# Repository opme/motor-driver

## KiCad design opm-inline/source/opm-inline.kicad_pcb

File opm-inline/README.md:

# motor-driver

This motor driver uses inline current sensing.  The driver chip TMC6200 has built in current sensing.

# Diagram

# TMC6200 Gate Driver

Design uses TMC6200 gate driver.  The datasheet is located at .  Below are some high level details about the gate driver.

Universal high voltage BLDC/PMSM/Servo MOSFET 3-halfbridge gate-driver with in line motor current sensing. External MOSFETs for up to 100A motor current. 3 Floating Sense Amplifiers with programmable gain (5, 10, 20)

Integrated current sense amplifiers eliminate costly sense amplifiers required for FOC controllers (recommended use for applications up to 10A, use external precision amplifiers for higher current with low sense resistor values)

THE TMC6200 OFFERS TWO BASIC MODES OF OPERATION: 

MODE 1: Stand-alone driver with pin configuration 
Enable this mode by tying low pin SPE. The interface pins allow a number of different settings for
BBM generation and sense amplifier amplification control. 

MODE 2: SPI controlled 
This mode allows detailed control over the protection, diagnostic and control features, e.g. for tuning
overcurrent detection. Enable this mode by tying high pin SPE.

The driver integrates a four-level temperature sensor (120°C pre-warning and selectable 136°C / 143°C / 150°C thermal shutdown)

The TMC6200 protects the MOSFET power stages against a short circuit or overload condition by monitoring the voltage drop in the high-side MOSFETs, as well as the voltage drop in the low-side mosfets

# Design Discussion

Choice is to run in Mode 1 - Stand-alone driver with pin configuration.  See datasheet Figure 1.1 Standalone application using differential sensing.  Existing FOC algorithms should run without relying on the SPI interface.  Future versions could change if the controller firmware has a driver added for TMC6200. 

In this mode the SPI pins are used for configuration and not settings/diagnostics.  Setting SDO/Single to +VCC_IO allow signals to be set to DRV_EN.  This is also the case for the Drive Strength and the sense amplication.  In a 10A implementation we set sense amplification to 10 and 00 driver strength since we are using simialr mosfets that were tested in the datasheet.

Drive Strength:
CSN / IDRV0 and SCK / IDRV1 - 00: 0.5A 01: 0.5/1A, 10: 1A, 11: 1.5A, currently set to 00 for .5A

Sense Amplification:
SDI / AMPLx10 - Sense Amplification 0: 5, 1: 10, currently set to 10.

The TMC6200 IC current sensing is recommended to have a limit of 10A when using the internal sensing.  

The thermal design of the PCB is also designed for 10A max current.  The 10A limit is chosen to allow full SMT and single side hole through components with 1oz copper.

Heatsink over the gate driver and mosfets is required over a certain current.  28x28x20 is a standard heat sink size and is added to the pcb using silicon thermal glue.

Initial parts were selected based on the Trinamic reference designs that I have copied into this git repo.

Footprint for capacitors and resistors chosen as 0603 to make it easier to manufacture with low end SMD machines.

Parts are selected that are available in quantity from various resellers due to current chip shortage.  Avoided any parts that were only available in small quantities or not in stock.

Sense resistor selection. TMC6200 datasheet specifies different sense resistor selection.  Sense resistor of 005R0 with 10x amplification was selected for 15A max current 10A continuous.

In addition to the TMC6200 internal temperature sensor, there is a temperature sensor on the board.  The analog temperature signal is sent out the controller.

Mosfet selection.  Reference design has via for +VM connection through SMT pad.  This limits the vendor ability to manufacture the board and increases cost due to those needed to be capped in the manufacturing process.  Alternative is to put the via next to the SMT pad.

# Resistor for LED

Blue LED to show VCC power is on:
  VCC power has a range of 12V to 48V
  LED voltage is 3.1V and typical current is 5mA with absolute maximum of 25mA
  (48v - 3.1v)/ .005A = 8980 Ohm 
  (48v - 3.1v)/ .025A = 1788 Ohm
  2k resistor

RED LED for fault:  
  +VCC_IO can have a voltage between 3.3 and 5V
  (3.3v - 2.2v) / .005A = 220 Ohm
  (5v - 2.2v) / .005A = 560 Ohm
  200 Ohm resistor

# Design Discussion for TMC6200 Pins 

See TMC6200 datasheet for full documentation of pins.  Below is specific decisions taken when choice was given.

CLK 24 pin on the TMC6200 is tied to GND using short wire for internal clock.  This clock has accuracy of +-4%

Exposed die pad: Connect the exposed die pad to a GND plane. Provide as many as possible vias for heat transfer to GND plane.  Reference design has via for GND connection through SMT pad.  Since TMC chip will be manually added for first batch, these through hole vias were used.  If those are done by SMT in the future then some other solution for tying the pad to GRD may be needed.

Mosfet pads go to +VM but do not use hole through vias.  This limits the vendor ability to manufacture the board and increases cost due to those needed to be capped in the manufacturing process.  Alternative is to put the via next to the SMT pad which is done in this design.

# Part selection

| Type| Designator| Footprint| Discussion | 
| :---:  | :-:       | :-:      |  :-: |
| TerminalBlock_3_P5.08mm| U3| Libraries:TerminalBlock_bornier-3_P5.08mm| Should support 18A to 20A max current though design current is 10A | 
| 1nF/100V| C14 C12 C11| Capacitor_SMD:C_0603_1608Metric|  |
| TerminalBlock_2_P5.08mm| U2| Libraries:TerminalBlock_bornier-2_P5.08mm| |
| 330uF/63V| C15 C16| Capacitor_THT:C_Radial_D10.0mm_H20.0mm_P5.00mm| TMC6200 datasheet recommends 100uF of electroltyic capacitor for each amp of current expected.  Total 660 uF for 10 Amps included. 10000 hour life, low impedance, low ESR, high ripple current rating  |
| VCC_IO| J2| Connector_JST:JST_PH_B2B-PH-K_1x02_P2.00mm_Vertical| |
| 1000R/1%| R19 R21| Resistor_SMD:R_0603_1608Metric| |
| 19-217/GHC-YR1S2/3T| D1 D2| LED_SMD:LED_0603_1608Metric| |
| 150R/1%| R20| Resistor_SMD:R_0603_1608Metric| |
| 4700R/1%| R18 R17 R24| Resistor_SMD:R_0603_1608Metric| |
| 10000R/1%| R16| Resistor_SMD:R_0603_1608Metric| |
| 100nF/50V| C17 C20 C10| Capacitor_SMD:C_0603_1608Metric| |
| Temperature| J5| Connector_JST:JST_PH_B2B-PH-K_1x02_P2.00mm_Vertical| |
| PWMx6| J3| Connector_JST:JST_PH_B6B-PH-K_1x06_P2.00mm_Vertical| |
| 0R| R22| Resistor_SMD:R_0603_1608Metric| |
| 1500R/1%| R23| Resistor_SMD:R_0603_1608Metric| |
| Current Sensing| J6| Connector_JST:JST_PH_B3B-PH-K_1x03_P2.00mm_Vertical| |
| SPI/Info| J1| Connector_JST:JST_PH_B6B-PH-K_1x06_P2.00mm_Vertical| |
| 0R| R26| Resistor_SMD:R_0603_1608Metric| |
| 0Ω| R25| Resistor_SMD:R_0603_1608Metric| |
| 2.2uF/50V| C13 C19| Capacitor_SMD:C_0805_2012Metric| |
| 100nF/100V| C18| Capacitor_SMD:C_0805_2012Metric| |
| TMC6200-TA| IC1| Libraries:TMC6200-TA| |
| 2R2/1%| R4 R6 R11 R13 R3 R1| Resistor_SMD:R_0603_1608Metric| slope control resistors.  1Ohm to 2.2Ohm recommended for larger MOSFETs. |
| 10R/1%| R5 R12 R2| Resistor_SMD:R_0603_1608Metric| |
| 0R005/1%/1W| R9 R10 R14 R15 R7 R8| Resistor_SMD:R_1206_3216Metric| Use low inductivity SMD type, e.g. 1210 or 2512 resistor for RS|
| 4.7uF/100V| C8 C9 C7| Capacitor_SMD:C_1210_3225Metric| |
| 4.7uF/16V| C5 C4 C6| Capacitor_SMD:C_0603_1608Metric| Bootstrap capacitors.  for larger QG - use minimum 4.7µF on 12VOUT pin. QG is 59.5nC at VDS=48V, VGS=10V, ID=20A |
| 22nF/100V| C1| Capacitor_SMD:C_0603_1608Metric| |
| 100nF/100V| C2 C3| Capacitor_SMD:C_0603_1608Metric| |
| Power Mosfet 60V 100A  2.5 max Rds(on)| Q2 Q6 Q4 Q3 Q1 Q5| Libraries:PDFN-8| HYG025N06LS1C2, 60V minimum, 2.5ohm max Rds(on) and fast switching for lower heat dissipation, Max current > 30A|

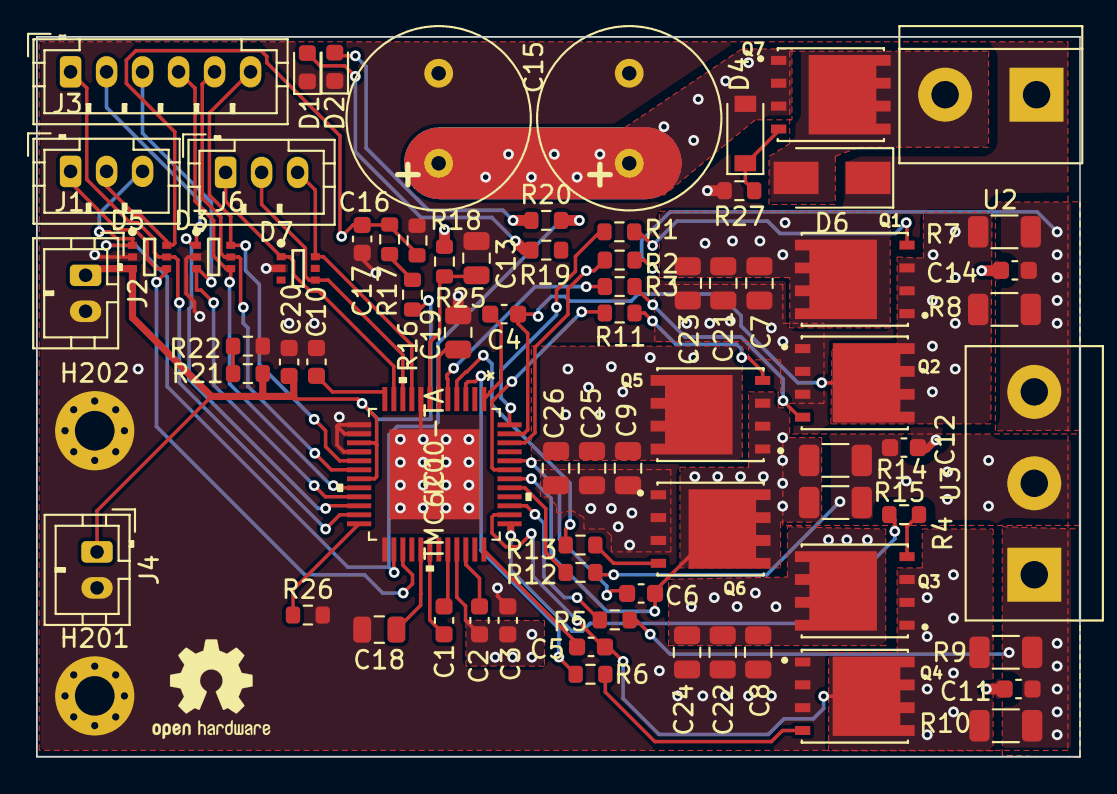
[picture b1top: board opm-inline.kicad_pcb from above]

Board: 4 copper layers, 58.0 x 40.0 mm, 76 parts (0 on the bottom side), 53 nets.

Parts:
C1: 22nF/100V; C_0603_1608Metric
C2, C3: 100nF/100V; C_0603_1608Metric
C4: 4.7uF/16V; C_0603_1608Metric
C5, C6: 4.7UF/16V; C_0603_1608Metric
C7, C8, C9, C21, C22, C23, C24, C25, C26: 1uF/100V; C_0805_2012Metric
C10, C17, C20: 100nF/50V; C_0603_1608Metric
C11, C12, C14: 1nF/100V; C_0603_1608Metric
C13, C19: 2.2uF/50V; C_0805_2012Metric
C15, C16: 330uF/63V; C_Radial_D10.0mm_H20.0mm_P5.00mm
C18: 100nF/100V; C_0805_2012Metric
D1: Blue LED; LED_0603_1608Metric
D2: Red LED; LED_0603_1608Metric
D3, D5, D7: NUP4114UCW1T2G
D4: 10V; D_SOD-123
D6: TVS DIODE; D_SMA
H201, H202: MountingHole; MountingHole_2.2mm_M2_Pad_Via
HS1: Heatsink; OSHW-Logo2_7.3x6mm_SilkScreen
IC1: TMC6200-TA
J1: Info; JST_PH_B3B-PH-K_1x03_P2.00mm_Vertical
J2: VCC_IO; JST_PH_B2B-PH-K_1x02_P2.00mm_Vertical
J3: PWMx6; JST_PH_B6B-PH-K_1x06_P2.00mm_Vertical
J4: Fan; JST_PH_B2B-PH-K_1x02_P2.00mm_Vertical
J6: Current Sensing; JST_PH_B3B-PH-K_1x03_P2.00mm_Vertical
Q1, Q2, Q3, Q4, Q5, Q6: HYG025N06LS1C2; PDFN-8
Q7: WSD90P06DN56; PDFN-8
R1, R3, R4, R6, R11, R13: 2R2/1%; R_0603_1608Metric
R2, R5, R12: 10R/1%; R_0603_1608Metric
R7, R8, R9, R10, R14, R15: 0R005/1%/1W; R_1206_3216Metric
R16: 10000R/1%; R_0603_1608Metric
R17, R18: 4700R/1%; R_0603_1608Metric
R19: 2KR/1%; R_0603_1608Metric
R20: 200R/1%; R_0603_1608Metric
R21: 1000R/1%; R_0603_1608Metric
R22, R26: 0R; R_0603_1608Metric
R25: 0Ω; R_0603_1608Metric
R27: 100KR; R_0603_1608Metric
U2: TerminalBlock_2_P5.08mm; TerminalBlock_bornier-2_P5.08mm
U3: TerminalBlock_3_P5.08mm; TerminalBlock_bornier-3_P5.08mm

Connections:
/5Vout: C13.1, IC1.7 (5VOUT), R25.1
/12Vout: C19.1, IC1.6 (12VOUT)
/+VCC_IO: C20.1, D5.3 (K), IC1.15 (SDI/AMPLx10), IC1.19 (VCC_IO), J2.1, J4.1, R16.1, R21.1
/+VM: C2.1, C3.1, C7.1, C8.1, C9.1, C15.1, C16.1, C21.1, C22.1, C23.1, C24.1, C25.1, C26.1, D4.2 (K), IC1.33 (VS), Q1.5 (D), Q1.6 (D), Q1.7 (D), Q1.8 (D), Q3.5 (D), Q3.6 (D), Q3.7 (D), Q3.8 (D), Q5.5 (D), Q5.6 (D), Q5.7 (D), Q5.8 (D), Q7.1 (S), Q7.2 (S), Q7.3 (S), R25.2
/ADC_I_u: D7.6 (K), IC1.9 (CURU), J6.3
/ADC_I_v: D7.4 (K), IC1.10 (CURV), J6.2
/ADC_I_w: D7.1 (K), IC1.11 (CURW), J6.1
/Connectors/VOFS: R21.2, R22.1
/DRV_EN: D5.4 (K), IC1.27 (DRV_EN), J1.1
/FAULT: D5.1 (K), IC1.26 (FAULT), J1.3, R20.2
/Motor Driver/VOFS: C10.1, IC1.12 (VOFS/TEST)
/TEMP_PCB: C17.1, D5.6 (K), J1.2, R17.2, R18.1
/U: C14.1, R2.1, R7.1, R8.1, U3.3
/UH: D3.6 (K), IC1.17 (UH), J3.6
/UL: D3.5 (K), IC1.18 (UL), J3.5
/V: C12.1, R12.1, R14.1, R15.1, U3.2
/VH: D3.4 (K), IC1.20 (VH), J3.4
/VL: D3.3 (K), IC1.21 (VL), J3.3
/VSA: C18.1, IC1.29 (VSA)
/W: C11.1, R5.1, R9.1, R10.1, U3.1
/WH: D3.1 (K), IC1.22 (WH), J3.2
/WL: D5.5 (K), IC1.23 (WL), J3.1
GND: C3.2, C7.2, C8.2, C9.2, C10.2, C11.2, C12.2, C13.2, C14.2, C15.2, C16.2, C17.2, C18.2, C19.2, C20.2, C21.2, C22.2, C23.2, C24.2, C25.2, C26.2, D1.1 (K), D2.1 (K), D3.2 (A), D5.2 (A), D6.1 (A), D7.2 (A), H201.1, H202.1, IC1.8 (GNDA), IC1.13 (CS/IDRV0), IC1.14 (SCK/IDRV1), IC1.16 (SDO_SINGLE), IC1.25 (SPE), IC1.EPAD, J2.2, J4.2, Q2.1 (S), Q2.2 (S), Q2.3 (S), Q4.1 (S), Q4.2 (S), Q4.3 (S), Q6.1 (S), Q6.2 (S), Q6.3 (S), R18.2, R22.2, R26.2, R27.2, U2.1
unnamed: C1.1, IC1.30 (CPO)
unnamed: C1.2, IC1.32 (CPI)
unnamed: C2.2, IC1.34 (VCP)
unnamed: C4.1, IC1.47 (U), Q1.1 (S), Q1.2 (S), Q1.3 (S), Q2.5 (D), Q2.6 (D), Q2.7 (D), Q2.8 (D), R7.2, R8.2
unnamed: C4.2, IC1.1 (CU)
unnamed: C5.1, IC1.36 (CW)
unnamed: C5.2, IC1.38 (W), Q3.1 (S), Q3.2 (S), Q3.3 (S), Q4.5 (D), Q4.6 (D), Q4.7 (D), Q4.8 (D), R9.2, R10.2
unnamed: C6.1, IC1.42 (V), Q5.1 (S), Q5.2 (S), Q5.3 (S), Q6.5 (D), Q6.6 (D), Q6.7 (D), Q6.8 (D), R14.2, R15.2
unnamed: C6.2, IC1.44 (CV)
unnamed: D1.2 (A), R19.1
unnamed: D2.2 (A), R20.1
unnamed: D4.1 (A), Q7.4 (G), R27.1
unnamed: D6.2 (K), Q7.5 (D), Q7.6 (D), Q7.7 (D), Q7.8 (D), U2.2
unnamed: IC1.3 (LSW), R6.2
unnamed: IC1.4 (LSV), R13.2
unnamed: IC1.5 (LSU), R3.2
unnamed: IC1.24 (CLK), R26.1
unnamed: IC1.37 (HSW), R4.2
unnamed: IC1.39 (WSENSE), R5.2
unnamed: IC1.41 (VSENSE), R12.2
unnamed: IC1.43 (HSV), R11.2
unnamed: IC1.46 (USENSE), R2.2
unnamed: IC1.48 (HSU), R1.2
unnamed: Q1.4 (G), R1.1
unnamed: Q2.4 (G), R3.1
unnamed: Q3.4 (G), R4.1
unnamed: Q4.4 (G), R6.1
unnamed: Q5.4 (G), R11.1
unnamed: Q6.4 (G), R13.1
unnamed: R16.2, R17.1

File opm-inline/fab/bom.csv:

Comment,Designator,Footprint,LCSC
0R,R26,Resistor_SMD:R_0603_1608Metric,C21189
100nF/50V,"C20,C10,C17",Capacitor_SMD:C_0603_1608Metric,C14663
0Ω,R25,Resistor_SMD:R_0603_1608Metric,C21189
2.2uF/50V,"C13,C19",Capacitor_SMD:C_0805_2012Metric,C49217
100nF/100V,C18,Capacitor_SMD:C_0805_2012Metric,C106243
TMC6200-TA,IC1,Libraries:TMC6200-TA,
2R2/1%,"R4,R6,R11,R13,R3,R1",Resistor_SMD:R_0603_1608Metric,C22939
10R/1%,"R5,R12,R2",Resistor_SMD:R_0603_1608Metric,C22859
0R005/1%/1W,"R9,R10,R14,R15,R7,R8",Resistor_SMD:R_1206_3216Metric,C601096
4.7UF/16V,"C5,C6",Capacitor_SMD:C_0603_1608Metric,C19666
22nF/100V,C1,Capacitor_SMD:C_0603_1608Metric,C313105
100nF/100V,"C2,C3",Capacitor_SMD:C_0603_1608Metric,C106243
4.7uF/16V,C4,Capacitor_SMD:C_0603_1608Metric,C19666
HYG025N06LS1C2,"Q2,Q6,Q4,Q3,Q1,Q5",Libraries:PDFN-8,C2827231
1uF/100V,"C9,C7,C8,C21,C23,C25,C26,C22,C24",Capacitor_SMD:C_0805_2012Metric,C697607
TerminalBlock_3_P5.08mm,U3,Libraries:TerminalBlock_bornier-3_P5.08mm,C72334
1nF/100V,"C14,C12,C11",Capacitor_SMD:C_0603_1608Metric,C342905
TerminalBlock_2_P5.08mm,U2,Libraries:TerminalBlock_bornier-2_P5.08mm,C8465
330uF/63V,"C15,C16",Capacitor_THT:C_Radial_D10.0mm_H20.0mm_P5.00mm,C338235
VCC_IO,J2,Connector_JST:JST_PH_B2B-PH-K_1x02_P2.00mm_Vertical,C131337
1000R/1%,"R19,R21",Resistor_SMD:R_0603_1608Metric,C21190
Green LED,D1,LED_SMD:LED_0603_1608Metric,C72043
150R/1%,R20,Resistor_SMD:R_0603_1608Metric,C22808
Red LED,D2,LED_SMD:LED_0603_1608Metric,C2286
4700R/1%,"R18,R17,R24",Resistor_SMD:R_0603_1608Metric,C23162
10000R/1%,R16,Resistor_SMD:R_0603_1608Metric,C13564
PWMx6,J3,Connector_JST:JST_PH_B6B-PH-K_1x06_P2.00mm_Vertical,C265365
0R,R22,Resistor_SMD:R_0603_1608Metric,
1500R/1%,R23,Resistor_SMD:R_0603_1608Metric,C22843
Current Sensing,J6,Connector_JST:JST_PH_B3B-PH-K_1x03_P2.00mm_Vertical,C131339
Fan,J4,Connector_JST:JST_PH_B2B-PH-K_1x02_P2.00mm_Vertical,C131337
Info,J1,Connector_JST:JST_PH_B3B-PH-K_1x03_P2.00mm_Vertical,C131339
100KR,R27,Resistor_SMD:R_0603_1608Metric,C25803
10V,D4,Diode_SMD:D_SOD-123,C82084
WSD90P06DN56,Q7,Libraries:PDFN-8,C719104
NUP4114UCW1T2G,"D5,D3,D7",Libraries:NUP4114UCW1T2G,C463643
TVS DIODE,D6,Diode_SMD:D_SMA,C523249

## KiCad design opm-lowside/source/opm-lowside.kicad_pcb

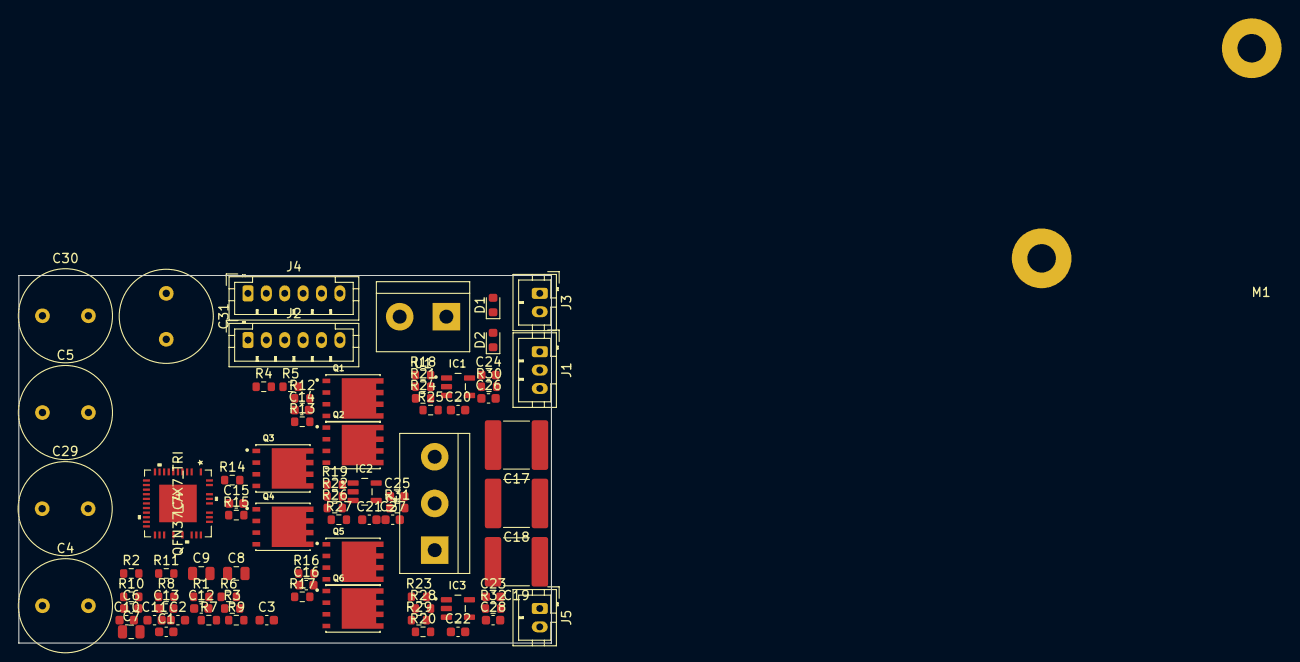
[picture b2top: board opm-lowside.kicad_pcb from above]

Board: 2 copper layers, 58.0 x 40.0 mm, 84 parts (0 on the bottom side), 65 nets, no tracks yet.

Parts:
C1, C2, C3: 1nF/100V; C_0603_1608Metric
C4, C5, C29, C30, C31: 330uF/63V; C_Radial_D10.0mm_H20.0mm_P5.00mm
C6, C10: 100nF/50V; C_0603_1608Metric
C7: 100nF/100V; C_0805_2012Metric
C8, C9: 2,2uF/50V; C_0805_2012Metric
C11: 22nF/100V; C_0603_1608Metric
C12, C13: 100nF/100V; C_0603_1608Metric
C14, C15, C16: 470nF/16V; C_0603_1608Metric
C17, C18, C19: 10uF/100V; C_2220_5650Metric
C20, C21, C22: 3300pF; C_0603_1608Metric
C23, C24, C25: 100nF/10V; C_0603_1608Metric
C26, C27, C28: 1nF/16V; C_0603_1608Metric
D1, D2: 19-217/GHC-YR1S2/3T; LED_0603_1608Metric
HS1: Heatsink; Heatsink_30x30mm_2xFixation3mm
IC1, IC2, IC3: INA180A3IDBVR; SOT95P280X145-5N
IC4: QFN37_7X7_TRI; TMC6100-LA
J1: Current Sensing; JST_PH_B3B-PH-K_1x03_P2.00mm_Vertical
J2: SPI/Info; JST_PH_B6B-PH-K_1x06_P2.00mm_Vertical
J3: VCC_IO; JST_PH_B2B-PH-K_1x02_P2.00mm_Vertical
J4: PWMx6; JST_PH_B6B-PH-K_1x06_P2.00mm_Vertical
J5: Temperature; JST_PH_B2B-PH-K_1x02_P2.00mm_Vertical
M1: Fan; Fan_3010
Q1, Q2, Q3, Q4, Q5, Q6: HYG025N06LS1C2; PDFN-8
R1: 10000R/1%; R_0603_1608Metric
R2, R3, R9: 4700R/1%; R_0603_1608Metric
R4, R6: 1000R/1%; R_0603_1608Metric
R5: 150R/1%; R_0603_1608Metric
R7, R10, R11: 0R; R_0603_1608Metric
R8: 1500R/1%; R_0603_1608Metric
R12, R13, R14, R15, R16, R17: 2.2R/1%; R_0603_1608Metric
R18, R19, R20, R21, R22, R23: R001/1%; R_0603_1608Metric
R24, R25, R26, R27, R28, R29: 10R/1%; R_0603_1608Metric
R30, R31, R32: 100R/5%; R_0603_1608Metric
U1: TerminalBlock_2_P5.08mm; TerminalBlock_bornier-2_P5.08mm
U2: TerminalBlock_3_P5.08mm; TerminalBlock_bornier-3_P5.08mm

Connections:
+5V: C1.2, C2.2, C3.2, C4.2, C5.2, C6.2, C7.2, C8.2, C9.2, C10.2, C12.1, C17.2, C18.2, C19.2, C23.1, C24.1, C25.1, C26.2, C27.2, C28.2, C29.2, C30.2, C31.2, D1.1, D2.1, IC1.2, IC2.2, IC3.2, IC4.8, IC4.9, J3.2, J5.2, R3.2, R7.2, R9.2, R11.2, R18.2, R19.2, R21.2, R22.2, R25.2, R27.2, U1.1
/5Vout: C9.1, IC4.7
/12Vout: C8.1, IC4.6
/+VM: C4.1, C5.1, C12.2, C13.2, C17.1, C18.1, C19.1, C29.1, C30.1, C31.1, IC4.28, Q1.1, Q1.2, Q1.3, Q3.1, Q3.2, Q3.3, Q5.1, Q5.2, Q5.3, U1.2
/+Vcc_IO: C10.1, IC4.16
/Connectors/+VCC_IO: R6.1, R8.1
/Connectors/VOFS: R6.2, R7.1
/DRV_EN: IC4.24, J2.5
/SPE: IC4.22, R8.2, R9.1
/U: C3.1, U2.3
/UH: IC4.14, J4.6
/UL: IC4.15, J4.5
/V: C2.1, U2.2
/VCP: C13.1, IC4.29
/VH: IC4.17, J4.4
/VL: IC4.18, J4.3
/VSA: C7.1, IC4.25, R10.1
/W: C1.1, U2.1
/WH: IC4.19, J4.2
/WL: IC4.20, J4.1
/~CS_DRIVER: IC4.10, J2.1
unnamed: C6.1, J5.1, R2.2, R3.1
unnamed: C11.1, IC4.27
unnamed: C11.2, IC4.26
unnamed: C14.1, IC4.36, Q1.5, Q1.6, Q1.7, Q1.8, Q2.1, Q2.2, Q2.3
unnamed: C14.2, IC4.1
unnamed: C15.1, IC4.33, Q3.5, Q3.6, Q3.7, Q3.8, Q4.1, Q4.2, Q4.3
unnamed: C15.2, IC4.35
unnamed: C16.1, IC4.32, Q5.5, Q5.6, Q5.7, Q5.8, Q6.1, Q6.2, Q6.3
unnamed: C16.2, IC4.30
unnamed: C20.1, IC1.3, R24.1
unnamed: C20.2, IC1.4, R25.1
unnamed: C21.1, IC2.3, R26.1
unnamed: C21.2, IC2.4, R27.1
unnamed: C22.1, IC3.3, R28.1
unnamed: C22.2, IC3.4, R29.1
unnamed: C23.2, IC3.5
unnamed: C24.2, IC1.5
unnamed: C25.2, IC2.5
unnamed: D1.2, R4.1
unnamed: D2.2, R5.1
unnamed: IC1.1, R30.2
unnamed: IC2.1, R31.2
unnamed: IC3.1, R32.2
unnamed: IC4.3, R17.2
unnamed: IC4.4, R15.2
unnamed: IC4.5, R13.2
unnamed: IC4.21, R11.1
unnamed: IC4.31, R16.2
unnamed: IC4.34, R14.2
unnamed: IC4.37, R12.2
unnamed: Q1.4, R12.1
unnamed: Q2.4, R13.1
unnamed: Q2.5, Q2.6, Q2.7, Q2.8, R18.1, R21.1, R24.2
unnamed: Q3.4, R14.1
unnamed: Q4.4, R15.1
unnamed: Q4.5, Q4.6, Q4.7, Q4.8, R19.1, R22.1, R26.2
unnamed: Q5.4, R16.1
unnamed: Q6.4, R17.1
unnamed: Q6.5, Q6.6, Q6.7, Q6.8, R20.1, R23.1, R28.2
unnamed: R1.2, R2.1
unnamed: R20.2, R23.2, R29.2
U-IA-IDC: C26.1, R30.1
V-IA-IDC: C27.1, R31.1
W-IA-IDC: C28.1, R32.1

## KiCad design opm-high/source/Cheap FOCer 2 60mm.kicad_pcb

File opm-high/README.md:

# tmc6100 with low side current sensing

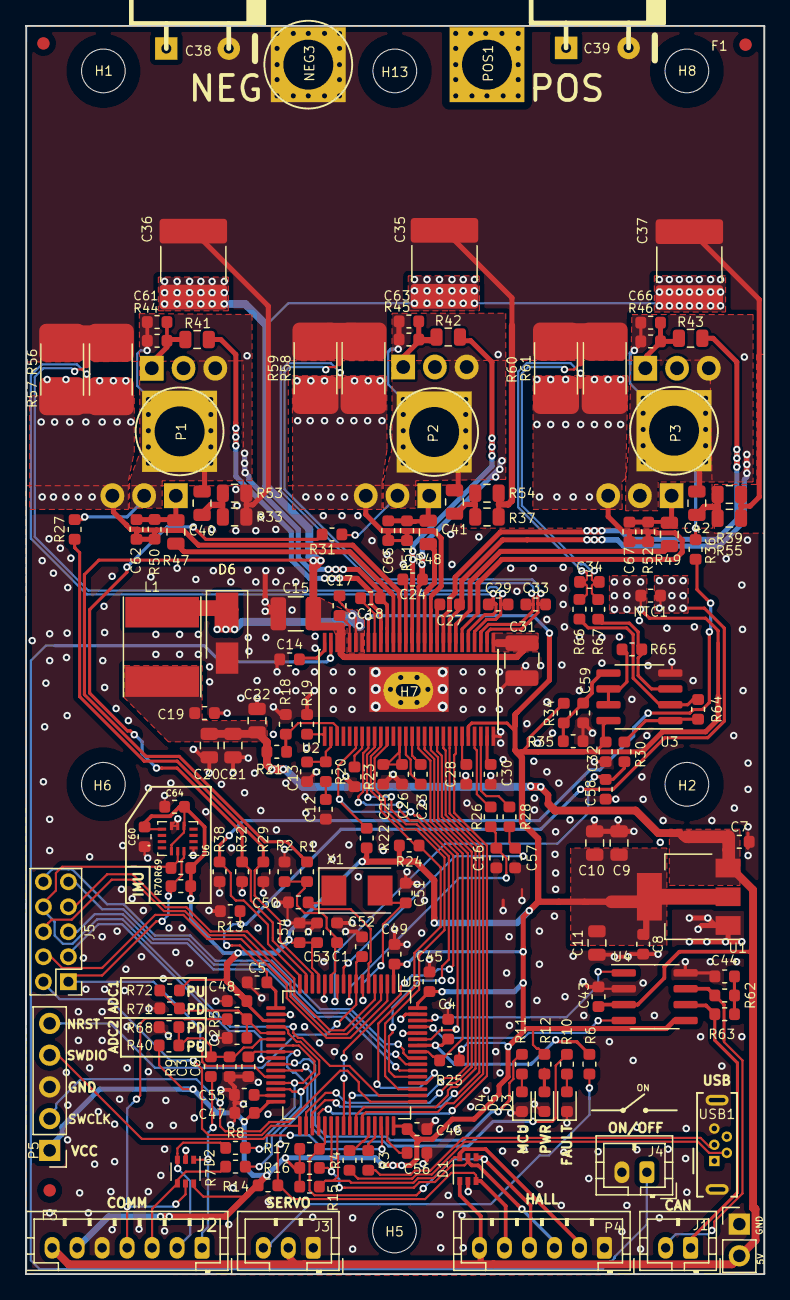
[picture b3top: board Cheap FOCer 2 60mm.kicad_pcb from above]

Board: 2 copper layers, 59.1 x 99.9 mm, 193 parts (0 on the bottom side), 110 nets.

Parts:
C1, C6, C7, C17, C32, C52, C59, C60, C64: 100n; C_0603_1608Metric
C2, C3: 0.01uF; C_0603_1608Metric
C4: .01uF; C_0603_1608Metric
C5, C8, C45, C46, C47, C48, C49, C53, C54, C55, C56: 2.2u; C_0603_1608Metric
C9, C10, C11: 22uF; C_0805_2012Metric
C12: 6.8n; C_0603_1608Metric
C13: 150p; C_0603_1608Metric
C14: 15nF; C_0603_1608Metric
C15, C31: 4.7uF, 100V; C_1210_3225Metric
C16, C29, C33, C34, C44, C57, C58, C61, C62, C63, C65, C66, C67: 1nF; C_0603_1608Metric
C18, C24, C27: 220n; C_0603_1608Metric
C19, C25, C26, C28, C30: 2.2uF; C_0603_1608Metric
C20, C21, C22: 22uf; C_0805_2012Metric
C23: 22n; C_0603_1608Metric
C35, C36, C37: 10uF, 100V; C_2220_5650Metric_Pad1.97x5.40mm_HandSolder
C38, C39: 330u, 63V; CP_10x20mm_hor_with_model_brd_edge
C40, C41, C42: 4.7nF, 100V; C_0805_2012Metric
C43: 0.1u; C_0603_1608Metric
C50, C51: 15p; C_0603_1608Metric
D1, D2: SMF05CT1G; SOT-363_SC-70-6
D3: RED; LED_0603_1608Metric
D4: GRN; LED_0603_1608Metric
D5: BLU; LED_0603_1608Metric
D6: 100v, 1A; D_SMA
F1, F2, F3: Fiducial; Fiducial_1mm_Dia_2mm_Outer
H1, H2, H5, H6, H7, H8, H13: MountingHole; MountingHole_3.2mm_M3_ISO14580_Pad
H3: SLJ; Sam_J
H4: Open Hardware Logo; OSHW-Logo2_9.8x8mm_SilkScreen
H9: KiCAD Logo; KiCad-Logo2_5mm_SilkScreen
J1: Conn_01x02; JST_PH_B2B-PH-K_1x02_P2.00mm_Vertical
J2: Conn_01x07; JST_PH_B7B-PH-K_1x07_P2.00mm_Vertical
J3: Conn_01x03; JST_PH_B3B-PH-K_1x03_P2.00mm_Vertical
J4: On/Off; JST_PH_B2B-PH-K_1x02_P2.00mm_Vertical
J5: UNUSED MCU PINS; PinHeader_2x05_P2.00mm_Vertical
J6: Conn_01x03; PinHeader_1x02_P2.54mm_Vertical
L1: 22u; L_Taiyo-Yuden_NR-60xx_HandSoldering
NEG3: MOTOR3; 1pin_4mm
NT1, NT2, NT3, NT4, NT5, NT6: Net-Tie_2; NetTie-2_SMD_Pad0.5mm
NTC1: NTC 10k; R_0603_1608Metric
P1, P2, P3: MOTOR1; 1pin_4mm
P4: HALL/Encoder; JST_PH_B6B-PH-K_1x06_P2.00mm_Vertical
P5: SWD; PinHeader_1x05_P2.54mm_Vertical
POS1: POS; 1pin_4mm
Q1, Q2, Q3, Q4, Q5, Q6: NCEP60T20; TO-220-3_Horizontal_TabUp_no_hole
R1, R27, R31, R36: 39k; R_0603_1608Metric
R2, R12, R15, R16, R17, R25, R29, R32, R38: 2k2; R_0603_1608Metric
R3, R4: 22R; R_0603_1608Metric
R5, R6, R7, R8, R9, R10, R11: 100R; R_0603_1608Metric
R13, R14, R22, R23, R34, R35: 10k; R_0603_1608Metric
R18: 3.3k; R_0603_1608Metric
R19: 220k; R_0603_1608Metric
R20: 15k; R_0603_1608Metric
R21: 18k; R_0603_1608Metric
R24, R26, R28, R30, R66, R67, R69, R70: 1k; R_0603_1608Metric
R33, R37, R39, R41, R42, R43, R47, R48, R49, R53, R54, R55: 10R; R_0805_2012Metric
R40, R68, R71, R72: DNP; R_0603_1608Metric
R44, R45, R46, R50, R51, R52: 4.7k; R_0603_1608Metric
R56, R57, R58, R59, R60, R61: 0.001R; R_2512_Yageo_big_pads
R62, R63: 60; R_0603_1608Metric
R64, R65: 20k; R_0603_1608Metric
U1: AMS1117-3.3; SOT-223-3_TabPin2
U2: DRV8301; HTSSOP-56-1EP_6.1x14mm_P0.5mm_EP3.61x6.35mm
U3: TP2604-SR; SOIC-8_3.9x4.9mm_P1.27mm
U4: TJA1051T/3/1J; SOIC-8_3.9x4.9mm_P1.27mm
U5: STM32F405RGT6; LQFP-64_10x10mm_P0.5mm
U6: BMI160; Bosch_LGA-14_3x2.5mm_P0.5mm
USB1: USB Micro U-D-M5DD-W-1; USB_Micro-B_Wuerth_614105150721_Vertical
X1: 8MHz 10ppm (X50328MSB2GI); Crystal_SMD_5032-2Pin_5.0x3.2mm

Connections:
+5V: C7.2, C19.2, C20.2, C21.2, C22.2, C43.1, D1.1, J2.7, J3.2, J6.2, L1.2, P4.6, R21.1, U1.3, U4.3
/CAN bus transceiver/CANH: J1.2, R62.1, U4.7
/CAN bus transceiver/CANL: J1.1, R63.2, U4.6
/CAN bus transceiver/CAN_RX: U4.4, U5.61
/CAN bus transceiver/CAN_TX: U4.1, U5.62
/Filters/HALL1_IN: D1.4, P4.4, R17.1, U5.37
/Filters/HALL2_IN: D1.5, P4.3, R16.1, U5.38
/Filters/TEMP_IN: C6.2, D1.3, P4.5, R14.1, U5.24
/HALL3: D1.6, P4.2, R15.1, U5.39
/MCU/ADC_TEMP: C5.1, NTC1.2, R13.1, U5.17
/MCU/AN_IN: C1.2, R1.2, R2.2, U5.11
/MCU/LED_RED: R10.2, U5.27
/MCU/MISO_ADC_EXT2: C3.2, R9.1, R40.2, R68.2, U5.22
/MCU/RX_SDA_NSS: R7.1, U5.20, U5.30
/MCU/SCK_ADC_EXT: C2.2, R5.1, R71.2, R72.2, U5.21
/MCU/TX_SCL_MOSI: R8.1, U5.23, U5.29
/MCU/USB_DM: R4.1, U5.44
/MCU/USB_DP: R3.1, U5.45
/MISO_RX_SCL_IN: D2.1, J2.1, R9.2
/Mosfet driver/BR_SO1: C16.2, R26.1
/Mosfet driver/BR_SO2: C57.2, R28.1
/Mosfet driver/BR_SO3: C58.2, R30.1
/Mosfet driver/EN_GATE: R25.1, U2.16
/Mosfet driver/FAULT: R22.2, U2.6
/Mosfet driver/GH_A: R41.2, U2.47
/Mosfet driver/GH_B: R42.2, U2.42
/Mosfet driver/GH_C: R43.2, U2.37
/Mosfet driver/GL_A: R47.2, U2.45
/Mosfet driver/GL_B: R48.2, U2.40
/Mosfet driver/GL_C: R49.2, U2.35
/Mosfet driver/H1_LOW: C62.2, NT1.2, Q4.3, R50.2, R56.2, R57.2, U2.44
/Mosfet driver/H1_VS: C18.2, C40.1, C61.2, P1.1, Q1.3, Q4.2, R27.1, R44.2, U2.46
/Mosfet driver/H2_LOW: C65.2, NT2.2, Q5.3, R51.1, R58.2, R59.2, U2.39
/Mosfet driver/H2_VS: C24.2, C41.1, C63.2, P2.1, Q2.3, Q5.2, R31.1, R45.1, U2.41
/Mosfet driver/H3_LOW: C67.2, NT3.2, Q6.3, R52.1, R60.2, R61.2, U2.34
/Mosfet driver/H3_VS: C27.2, C42.1, C66.2, P3.1, Q3.3, Q6.2, R36.1, R46.1, U2.36
/Mosfet driver/SDO: R24.1, U2.10
/Mosfet driver/SENS1: R27.2, R29.2
/Mosfet driver/SENS2: R31.2, R32.2
/Mosfet driver/SENS3: R36.2, R38.2
/RX_SDA_IN: D2.4, J2.3, R7.2
/SCK_ADC_EXT_IN: D2.5, J2.4, R5.2
/TX_SCL_MOSI_IN: D2.3, J2.2, R8.2
GND: C1.1, C2.1, C3.1, C4.1, C5.2, C6.1, C7.1, C8.2, C9.1, C10.1, C11.1, C12.1, C13.1, C14.2, C15.1, C16.1, C19.1, C20.1, C21.1, C22.1, C25.2, C26.2, C28.2, C30.1, C31.1, C32.1, C35.1, C36.1, C37.1, C38.2, C39.2, C43.2, C44.2, C45.1, C46.1, C47.1, C48.1, C49.1, C50.2, C51.2, C52.1, C53.1, C54.1, C55.2, C56.2, C57.1, C58.1, C59.2, C60.1, C64.1, D1.2, D2.2, D3.1, D4.1, D5.1, D6.2, H7.1, J2.5, J3.1, J4.2, J6.1, NEG3.1, NT4.2, NT5.2, NT6.2, P4.1, P5.3, R2.1, R13.2, R18.2, R19.2, R23.1, R29.1, R32.1, R33.1, R35.2, R37.1, R38.1, R39.1, R53.1, R54.1, R55.1, R56.1, R57.1, R58.1, R59.1, R60.1, R61.1, R68.1, R71.1, U1.1, U2.28, U2.57, U3.4, U4.2, U4.8, U5.12, U5.18, U5.60, U5.63, U6.1, U6.6, U6.7, USB1.5, USB1.6
NRST: C52.2, P5.5, U5.7
unnamed: C4.2, R6.1
unnamed: C12.2, R20.2
unnamed: C13.2, R20.1, U2.2
unnamed: C14.1, U2.56
unnamed: C17.1, U2.52
unnamed: C17.2, D6.1, L1.1, U2.50, U2.51
unnamed: C18.1, U2.48
unnamed: C23.1, U2.15
unnamed: C23.2, U2.14
unnamed: C24.1, U2.43
unnamed: C25.1, C26.1, U2.13
unnamed: C27.1, U2.38
unnamed: C28.1, U2.23
unnamed: C30.2, U2.27
unnamed: C40.2, R33.2, R53.2
unnamed: C41.2, R37.2, R54.2
unnamed: C42.2, R39.2, R55.2
unnamed: C44.1, R62.2, R63.1
unnamed: C50.1, U5.5, X1.1
unnamed: C51.1, U5.6, X1.2
unnamed: C55.1, U5.31
unnamed: C56.1, U5.47
unnamed: C59.1, R34.2, R35.1, U3.5
unnamed: C61.1, Q1.1, R41.1, R44.1
unnamed: C62.1, Q4.1, R47.1, R50.1
unnamed: C63.1, Q2.1, R42.1, R45.2
unnamed: C65.1, Q5.1, R48.1, R51.2
unnamed: C66.1, Q3.1, R43.1, R46.2
unnamed: C67.1, Q6.1, R49.1, R52.2
unnamed: D3.2, R10.1
unnamed: D4.2, R11.1
unnamed: D5.2, R12.1
unnamed: J3.3, R6.2
unnamed: J4.1, U2.55
unnamed: R3.2, USB1.3
unnamed: R4.2, USB1.2
unnamed: R18.1, R21.2, U2.3
unnamed: R19.1, U2.1
unnamed: R23.2, U2.7
unnamed: R26.2, U2.25
unnamed: R28.2, U2.26
unnamed: R30.2, R64.1, U3.1
unnamed: R64.2, R66.1, U3.2
unnamed: R65.1, U3.6, U3.7
unnamed: R65.2, R67.1, U3.3
PA15: J5.8, R69.2, U5.50, U6.13
PB2: J5.1, R70.1, U5.28, U6.14
PB3: J5.9, U5.55
PB4: J5.10, U5.56
PB12: J5.2, U5.33
PC5: J5.3, U5.25
PC13: J5.4, U5.2
PC14: J5.6, U5.3
PC15: J5.7, U5.4
PD2: J5.5, U5.54
SNA: C29.2, NT1.1, U2.33
SNB: C33.1, NT2.1, U2.31
SNC: C34.1, NT3.1, R66.2
SPA: C29.1, NT4.1, U2.32
SPB: C33.2, NT5.1, U2.30
SPC: C34.2, NT6.1, R67.2
SWCLK: P5.2, U5.49
SWDIO: P5.4, U5.46
VCC: C8.1, C9.2, C10.2, C11.2, C32.2, C45.2, C46.2, C47.2, C48.2, C49.2, C53.2, C54.2, C60.2, C64.2, D2.6, J2.6, NTC1.1, P5.1, R12.2, R14.2, R15.2, R16.2, R17.2, R22.1, R24.2, R25.2, R34.1, R40.1, R69.1, R70.2, R72.1, U1.2, U2.24, U2.49, U3.8, U4.5, U5.1, U5.13, U5.19, U5.32, U5.48, U5.64, U6.5, U6.8, U6.12
V_SUPPLY: C15.2, C31.2, C35.2, C36.2, C37.2, C38.1, C39.1, POS1.1, Q1.2, Q2.2, Q3.2, R1.1, U2.29, U2.53, U2.54

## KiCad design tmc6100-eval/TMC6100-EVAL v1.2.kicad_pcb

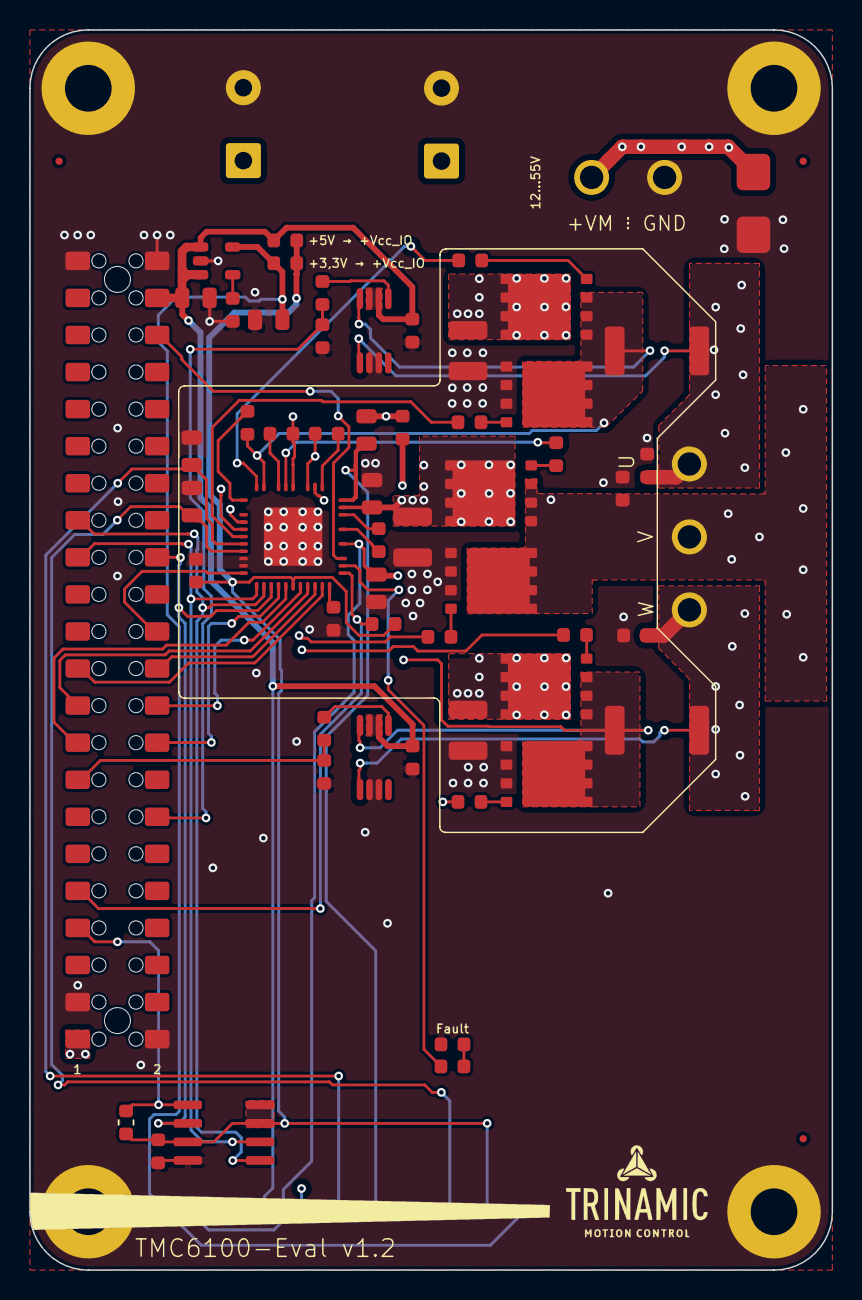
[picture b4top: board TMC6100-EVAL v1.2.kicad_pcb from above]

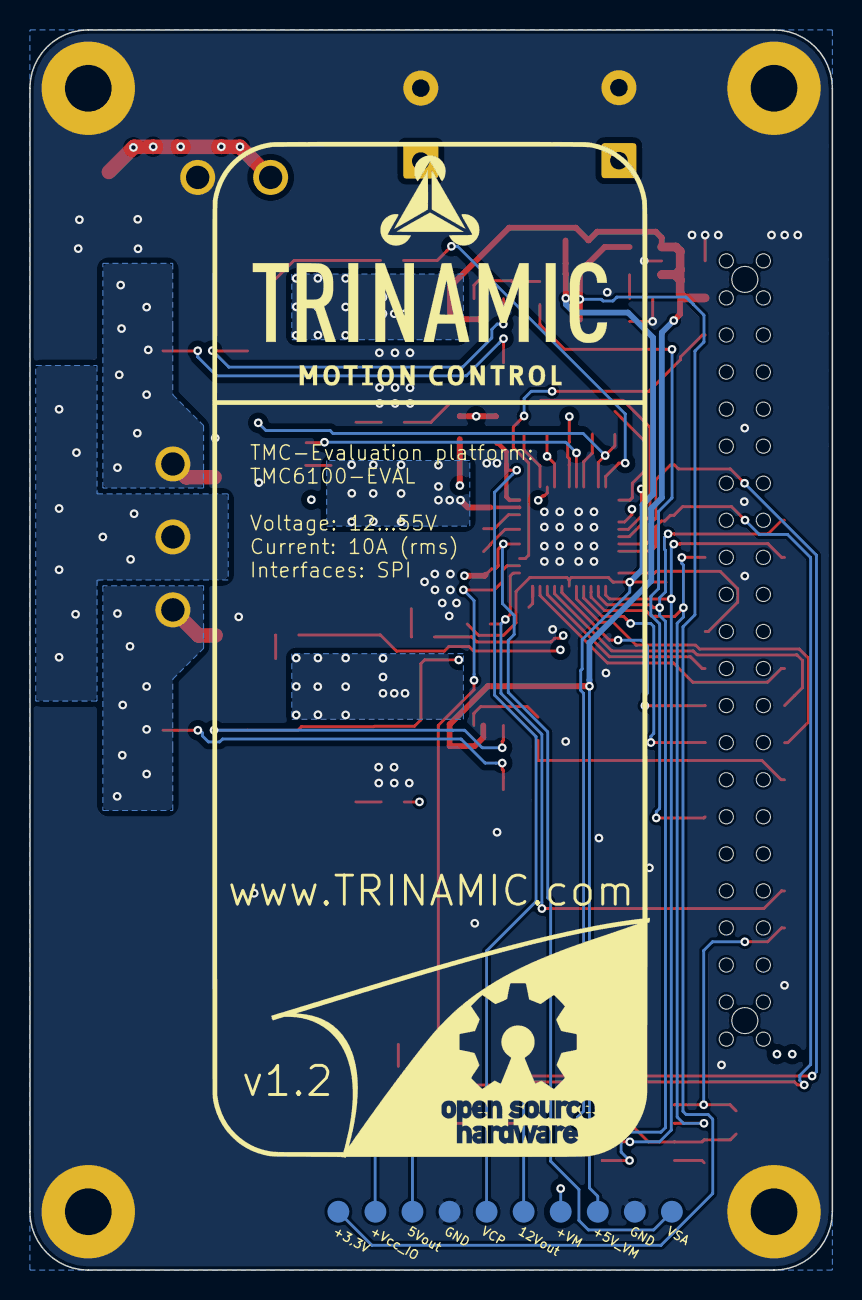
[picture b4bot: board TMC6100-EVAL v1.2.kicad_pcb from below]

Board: 4 copper layers, 55.0 x 85.0 mm, 76 parts (10 on the bottom side), 52 nets.

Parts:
C201, C202: 220μF/100V; CP_Radial_D12.5mm_P5.00mm
C203, C204, C205: 1nF/100V; C_0603_1608Metric
C301, C316: 100nF/16V; C_0603_1608Metric
C302, C317: 2,2nF/16V; C_0603_1608Metric
C303, C310, C318: 470nF/16V; C_0603_1608Metric
C304, C314, C319: 2,2μF/100V; C_1210_3225Metric
C305, C307, C311: 100nF/100V; C_0805_2012Metric
C306: 22nF/100V; C_0603_1608Metric
C312, C313: 2,2μF/50V; C_0805_2012Metric
C315, C404: 100nF/50V; C_0603_1608Metric
C401, C403: 4,7μF/16V; C_0805_2012Metric
C402: 10nF/16V; C_0603_1608Metric
D401: HSMC-C190; LED_0603_1608Metric
D402: SMBJ58A; D_SMB
H201, H202, H203, H204: MountingHole; MountingHole_3.2mm_M3_Pad
IC301: TMC6100-LA; QFN-44-1EP_7x7mm_P0.5mm_EP4x4mm
J201: W+P_46-3492-44-3-00-10-PPTR; Samtec_HLE-144-02-xxx-DV-BE-A_2x22_P2.54mm_Horizontal
Q301, Q302, Q303, Q304, Q305, Q306: BSC026N08NS5; TDSON-8-1
R203: 10kΩ/1%; R_0603_1608Metric
R301: 10kΩ/1%/0603; R_0603_1608Metric
R303, R317: 1kΩ/1%; R_0603_1608Metric
R304, R306, R310, R313, R318, R320: 2,2Ω/1%; R_0603_1608Metric
R305, R319: 3mΩ/1%/3W; R_2512_6332Metric
R311, R314, R401, R402: 0Ω; R_0603_1608Metric
R403: 150Ω/1%; R_0603_1608Metric
TP201, TP202, TP203, TP204, TP205, TP206, TP207, TP208, TP209, TP210: TestPoint; TestPoint_Pad_D1.5mm
U201: Metz_31330102
U203: Metz_31330103
U301, U303: AD8418; MSOP-8_3x3mm_P0.65mm
U401: LP2985-3.3; SOT-23-5
U402: AT25128B-SSHL-T8S1-L; SOIC-8_3.9x4.9mm_P1.27mm
fid201, fid202, fid203: fiducial; Fiducial_0.5mm_Dia_1mm_Outer

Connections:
/5Vout: C313.1, IC301.7, TP208.1
/12Vout: C312.1, IC301.6, TP205.1
/+3,3V: C403.1, R402.2, TP210.1, U401.5
/+5V_VM: C301.1, C316.1, C401.1, J201.42, R401.2, TP203.1, U301.6, U301.7, U303.6, U303.7, U401.1, U401.3
/+VM: C201.1, C202.1, C304.1, C305.2, C307.2, C314.1, C319.1, D402.1, IC301.28, J201.1, Q301.5, Q303.5, Q305.5, R311.2, TP204.1, U201.2
/+Vcc_IO: C315.1, C404.2, IC301.16, R203.2, R301.1, R401.1, R402.1, TP209.1, U402.3, U402.7, U402.8
/ADC_I_u: C302.1, J201.14, R303.1
/ADC_I_w: C317.1, J201.15, R317.1
/DRV_EN: IC301.24, J201.40
/Fault: IC301.23, R403.2
/SPE: IC301.22, J201.9, R203.1
/SPI2_MISO: IC301.13, J201.28, U402.2
/SPI2_MOSI: IC301.12, J201.29, U402.5
/SPI2_SCK: IC301.11, J201.27, U402.6
/U: C203.1, R305.1, U203.3, U301.1
/UH: IC301.14, J201.18
/UL: IC301.15, J201.17
/V: C204.1, C310.1, IC301.33, Q303.1, Q303.2, Q303.3, Q304.5, U203.2
/VCP: C307.1, IC301.29, TP206.1
/VH: IC301.17, J201.20
/VL: IC301.18, J201.19
/VSA: C311.1, IC301.25, R311.1, TP201.1
/W: C205.1, R319.1, U203.1, U303.1
/WH: IC301.19, J201.22
/WL: IC301.20, J201.21
/~CS_DRIVER: IC301.10, J201.24
/~CS_EEPROM: J201.7, R301.2, U402.1
GND: C201.2, C202.2, C203.2, C204.2, C205.2, C301.2, C302.2, C304.2, C305.1, C311.2, C312.2, C313.2, C314.2, C315.2, C316.2, C317.2, C319.2, C401.2, C402.2, C403.2, C404.1, D401.1, D402.2, H201.1, H202.1, H203.1, H204.1, IC301.8, IC301.9, IC301.PAD, J201.2, J201.3, J201.43, J201.44, Q302.1, Q302.2, Q302.3, Q304.1, Q304.2, Q304.3, Q306.1, Q306.2, Q306.3, R314.2, TP202.1, TP207.1, U201.1, U301.2, U301.3, U303.2, U303.3, U401.2, U402.4
unnamed: C303.1, IC301.36, Q301.1, Q301.2, Q301.3, Q302.5, R305.2, U301.8
unnamed: C303.2, IC301.1
unnamed: C306.1, IC301.27
unnamed: C306.2, IC301.26
unnamed: C310.2, IC301.35
unnamed: C318.1, IC301.32, Q305.1, Q305.2, Q305.3, Q306.5, R319.2, U303.8
unnamed: C318.2, IC301.30
unnamed: C402.1, U401.4
unnamed: D401.2, R403.1
unnamed: IC301.3, R320.2
unnamed: IC301.4, R313.2
unnamed: IC301.5, R306.2
unnamed: IC301.21, R314.1
unnamed: IC301.31, R318.2
unnamed: IC301.34, R310.2
unnamed: IC301.37, R304.2
unnamed: Q301.4, R304.1
unnamed: Q302.4, R306.1
unnamed: Q303.4, R310.1
unnamed: Q304.4, R313.1
unnamed: Q305.4, R318.1
unnamed: Q306.4, R320.1
unnamed: R303.2, U301.5
unnamed: R317.2, U303.5

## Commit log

2021-12-13 tmc6100-eval
2021-12-13 add readme
2021-12-13 remove unneeded
2021-12-13 cleanup
2021-12-13 add libs
2021-12-13 add tmc libs
2021-12-13 change path
2021-12-13 rename files
2021-12-13 remove files
2021-12-14 add high current inline
2021-12-14 remove some bak files
2021-12-14 fix libs
2021-12-14 add tmc6200
2021-12-14 add lib
2021-12-15 update for current sense
2021-12-15 annotate
2021-12-16 more cleaning
2021-12-16 add inline and cleanup
2021-12-16 some work on inline
2021-12-16 add some values
2021-12-16 more value updates
2021-12-16 update parts
2021-12-17 add more lssc basic parts
2021-12-17 update libs
2021-12-17 update connectors
2021-12-17 add fiducials
2021-12-17 add more parts
2021-12-19 remove regulator
2021-12-19 add headers
2021-12-19 prepare for pcb
2021-12-20 fix connections
2021-12-20 add new libs
2021-12-20 adc out headers
2021-12-20 add pcb
2021-12-20 add footprint
2021-12-20 update caps
2021-12-21 update resistors
2021-12-21 more layout work
2021-12-21 more placements
2021-12-21 some more layout
2021-12-24 more layout
2021-12-24 cleanup test path
2021-12-25 update from latest
2021-12-25 add panel
2021-12-25 add fabrication file
2021-12-25 fix some parts
2021-12-25 remove fiducials
2021-12-26 fix rail
2021-12-26 fix naming
2021-12-26 fix spacing
2021-12-26 adjust board size
2021-12-26 update from netlist
2021-12-26 add initial
2021-12-26 fixes
2021-12-26 first config
2021-12-26 heatsink
2021-12-26 add heatsink
2021-12-27 add step
2021-12-27 add fan
2021-12-27 add manf num
2021-12-27 update panel
2021-12-27 change spacing
2021-12-28 increase caps
2021-12-28 update position
2021-12-29 try routing
2021-12-31 more routing
2022-01-02 add readme to disuss design
2022-01-02 update bom
2022-01-02 add pic
2022-01-02 add image
2022-01-02 update connections
2022-01-03 use pins
2022-01-04 rearrange
2022-01-09 route tracks
2022-01-16 fab one only
2022-01-16 sample fab
2022-01-16 update fab
2022-01-16 fix current sense resistor
2022-01-16 align refs
2022-01-17 update back side copper pours
2022-01-18 fix vias
2022-01-19 fix missing track
2022-01-19 tie spe low for standalone
2022-01-21 upgrade to kicad6
2022-01-21 update design rules
2022-01-21 fabricate_one.sh
2022-01-21 fabricate.sh
2022-01-22 update 3d models
2022-01-22 cleanup tracks
2022-01-24 add version with mcu
2022-01-24 add mcu
2022-01-24 update mcu
2022-01-24 update for can
2022-01-25 add can
2022-01-27 add resistor info for led
2022-01-27 update led and resistor values
2022-01-27 updat resistor and led
2022-01-27 update led
2022-01-27 update cap
2022-01-27 add files
2022-01-27 remove net
2022-01-27 fix red led

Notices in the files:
parts and their libraries:
Copyright 2021 Accelerated Designs. All rights reserved.
